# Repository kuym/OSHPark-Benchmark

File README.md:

# Interesting PCB designs

## L4

Device with Nordic nRF51822, muRata Type-1BD SiP (containing Broadcom BCM43362 WiFi silicon and STM32F405 microcontroller) plus ultra-low-power STM32L052.  BLE and WiFi RF paths are shared with an RF switch (Skyworks SKY13370.)

## BGA64-500um

Breakout for STM32 microcontroller in 64BGA (8x8 balls at 0.5mm pitch) to breadboard-friendly packaging.

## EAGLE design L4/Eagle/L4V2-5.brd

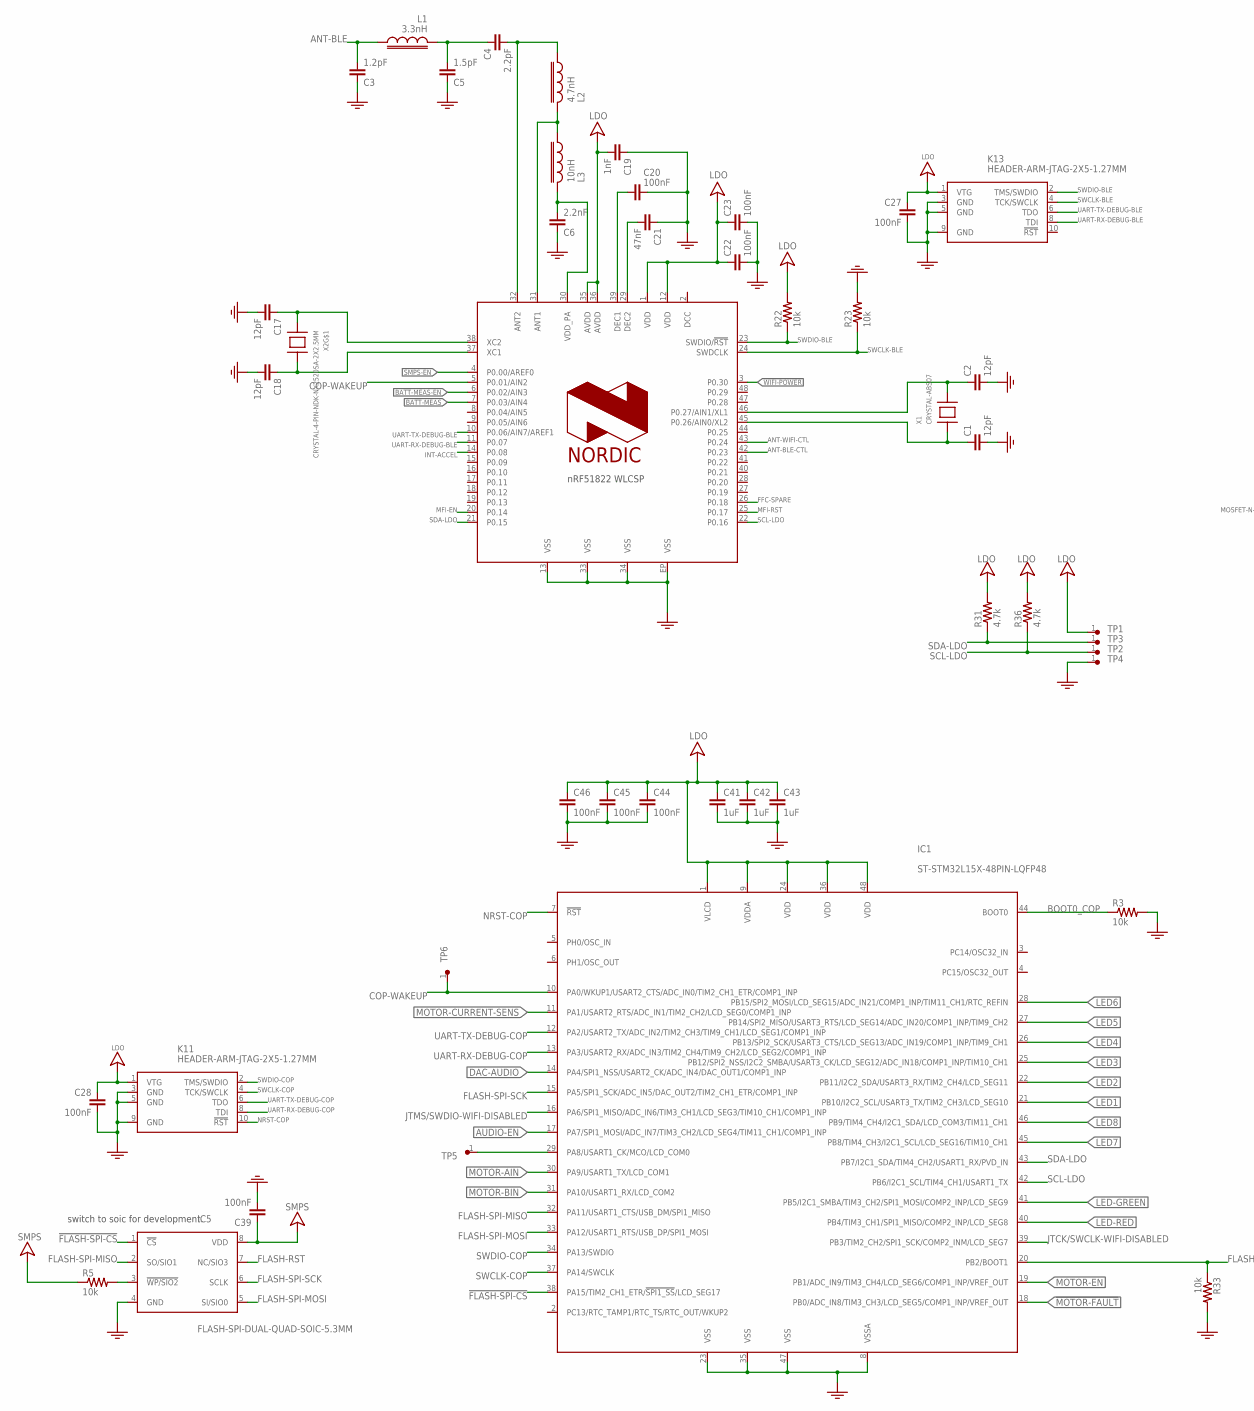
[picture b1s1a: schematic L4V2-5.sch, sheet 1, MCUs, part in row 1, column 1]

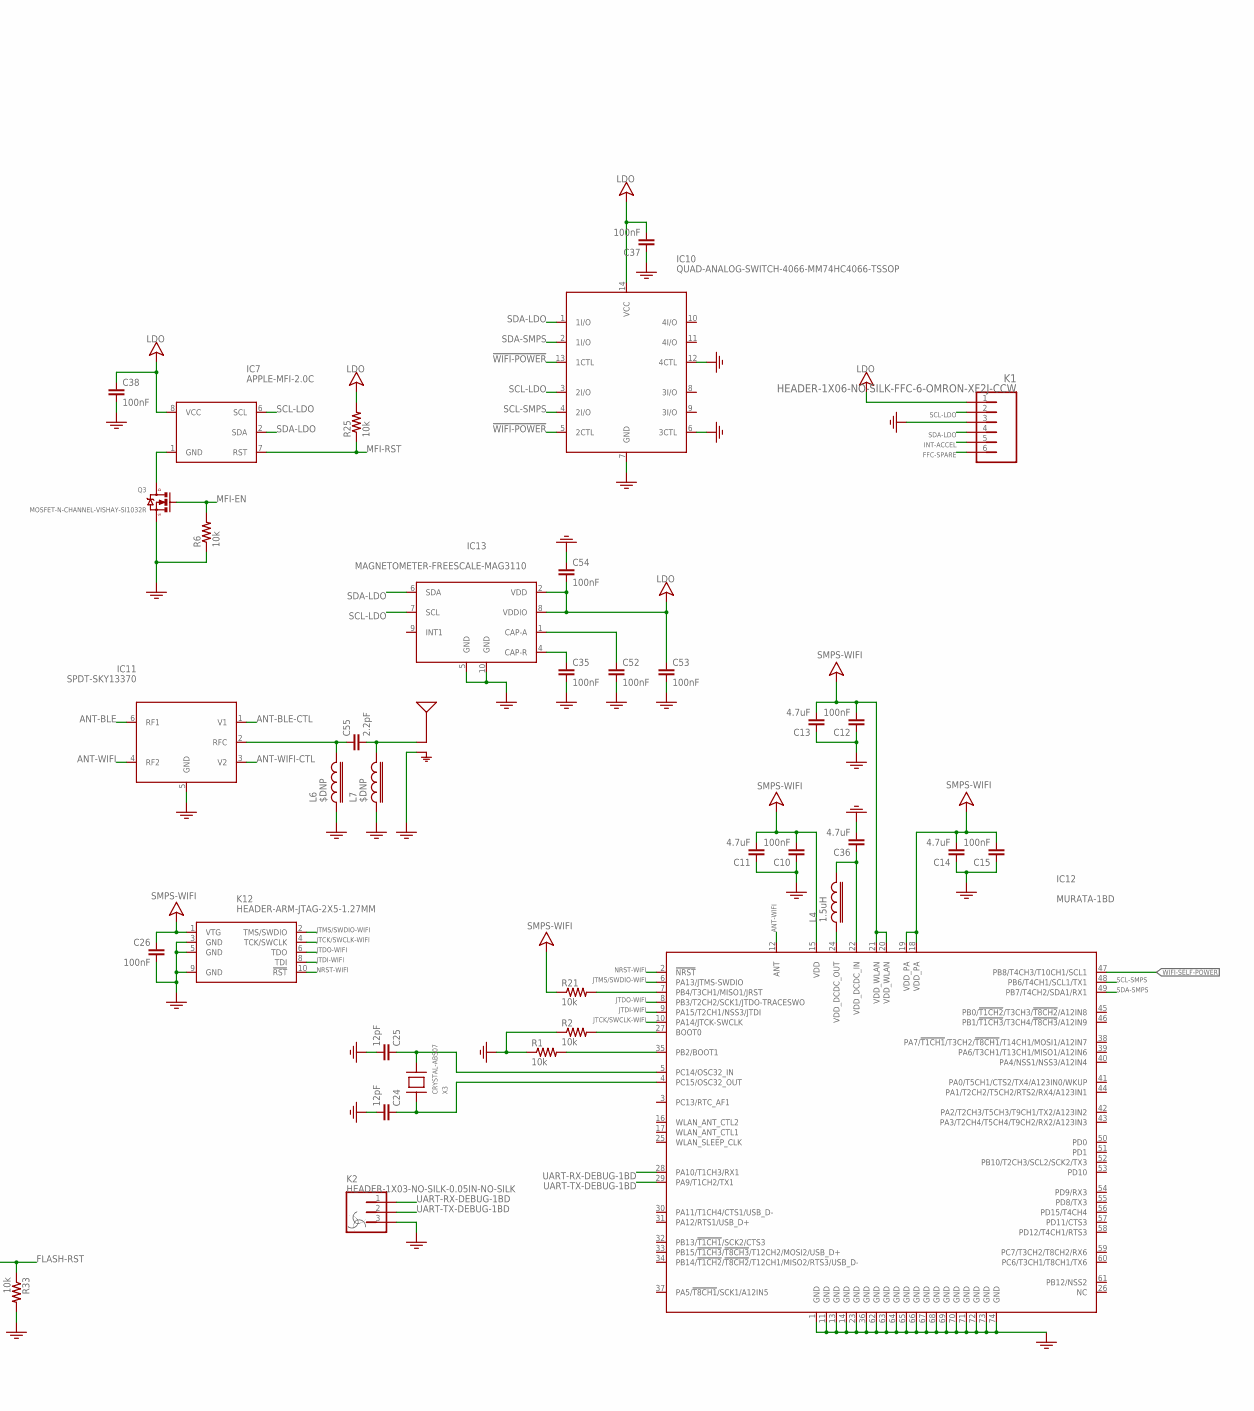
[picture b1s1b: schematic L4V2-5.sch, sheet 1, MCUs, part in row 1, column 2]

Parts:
ANT1: ANTENNA-WITH-GND-2.450GHZ-TI-AN043; ANTENNA-2.450GHZ-TI-AN043
C1, C2, C17, C18, C24, C25: 12pF; 0402
C3: 1.2pF; 0402
C4: 2.2pF; 0402
C5: 1.5pF; 0402
C6: 2.2nF; 0402
C10, C12, C15, C20, C22, C23, C26, C27, C28, C35, C37, C38, C39, C44, C45, C46, C52, C53, C54: 100nF; 0402
C11, C13, C14, C36: 4.7uF; 0402
C19: 1nF; 0402
C21: 47nF; 0402
C41, C42, C43: 1uF; 0402
C55: 2.2pF; 0402-MIN
IC1: ST-STM32L15X-48PIN-LQFP48; LQFP48-0.5MM
IC3: BLUETOOTH-4.0-SOC-NORDIC-NRF51822-QFN48; QFN48-5X5MM-0.4MM
IC5: FLASH-SPI-DUAL-QUAD-SOIC-5.3MM; SOIC8-5.3MM-MINIMAL
IC7: APPLE-MFI-2.0C; DFN8-2.5MMX2.5MM
IC10: QUAD-ANALOG-SWITCH-4066-MM74HC4066-TSSOP; TSSOP14
IC11: SPDT-SKY13370; DFN6-1.5MMX1.5MM
IC12: MURATA-1BD
IC13: MAGNETOMETER-FREESCALE-MAG3110; QFN10-2X2MM-FREESCALE-MAG3110
K1: HEADER-1X06-NO-SILK-FFC-6-OMRON-XF2J-CCW; HEADER-FFC-6-OMRON-XF2J-CCW
K2: HEADER-1X03-NO-SILK-0.05IN-NO-SILK; HEADER-1X03-0.05IN-NO-SILK
K11, K12, K13: HEADER-ARM-JTAG-2X5-1.27MM; HEADER-SMT-1.27MM-5X2-JTAG
L1: 3.3nH; 0402
L2: 4.7nH; 0402
L3: 10nH; 0402
L4: 1.5uH; 0805-WIDE
L6, L7: $DNP; 0402-MIN
Q3: MOSFET-N-CHANNEL-VISHAY-SI1032R; SC-75A
R1, R2, R3, R5, R6, R21, R22, R23, R25, R33: 10k; 0402
R31, R36: 4.7k; 0402
TP1, TP2, TP3, TP4, TP5, TP6: $DNP; TEST-POINT-0.75MM
X1, X3: CRYSTAL-ABS07; 1206-MIN
X2: CRYSTAL-4-PIN-NDK-NX2520SA-2X2.5MM; CRYSTAL-NDK-NX2025SA-2X2.5MM

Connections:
16MHZ-XTAL-IN: C18.2, IC3.37 (XC1), X2.1
16MHZ-XTAL-OUT: C17.2, IC3.38 (XC2), X2.3
32KHZ-XTAL-IN-BLE: C2.2, IC3.46 (P0.27/AIN1/XL1), X1.2
32KHZ-XTAL-IN-WIFI: C25.2, IC12.5 (PC14/OSC32_IN), X3.2
32KHZ-XTAL-OUT-BLE: C1.2, IC3.45 (P0.26/AIN0/XL2), X1.1
32KHZ-XTAL-OUT-WIFI: C24.2, IC12.4 (PC15/OSC32_OUT), X3.1
!FLASH-SPI-CS: IC1.38 (PA15/TIM2_CH1_ETR/!SPI1_SS!/LCD_SEG17), IC5.1 (!CS)
!MOTOR-FAULT: IC1.18 (PB0/ADC_IN8/TIM3_CH3/LCD_SEG5/COMP1_INP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); also elsewhere on the board
!WIFI-POWER: IC3.3 (P0.30), IC10.5 (2CTL), IC10.13 (1CTL); also elsewhere on the board
ANT-BLE: C3.1, IC11.6 (RF1), L1.2
ANT-BLE-CTL: IC3.42 (P0.23), IC11.1 (V1)
ANT-WIFI: IC11.4 (RF2), IC12.12 (ANT)
ANT-WIFI-CTL: IC3.43 (P0.24), IC11.3 (V2)
AUDIO-EN: IC1.17 (PA7/SPI1_MOSI/ADC_IN7/TIM3_CH2/LCD_SEG4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); also elsewhere on the board
BATT-MEAS: IC3.7 (P0.03/AIN4); also elsewhere on the board
BATT-MEAS-EN: IC3.6 (P0.02/AIN3); also elsewhere on the board
BOOT0_COP: IC1.44 (BOOT0), R3.1
COP-WAKEUP: IC1.10 (PA0/WKUP1/USART2_CTS/ADC_IN0/TIM2_CH1_E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), IC3.5 (P0.01/AIN2), TP6.1
DAC-AUDIO: IC1.14 (PA4/SPI1_NSS/USART2_CK/ADC_IN4/DAC_OUT1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); also elsewhere on the board
FFC-SPARE: IC3.26 (P0.18), K1.6
FLASH-RST: IC1.20 (PB2/BOOT1), IC5.7 (NC/SIO3), R33.1
FLASH-SPI-MISO: IC1.32 (PA11/USART1_CTS/USB_DM/SPI1_MISO), IC5.2 (SO/SIO1)
FLASH-SPI-MOSI: IC1.33 (PA12/USART1_RTS/USB_DP/SPI1_MOSI), IC5.5 (SI/SIO0)
FLASH-SPI-SCK: IC1.15 (PA5/SPI1_SCK/ADC_IN5/DAC_OUT2/TIM2_CH1_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), IC5.6 (SCLK)
GND: ANT1.RFGND (GND), C1.1, C2.1, C3.2, C5.2, C6.2, C10.2, C11.2, C12.2, C13.2, C14.2, C15.2, C17.1, C18.1, C19.2, C20.2, C21.2, C22.1, C23.1, C24.1, C25.1, C26.1, C27.1, C28.1, C35.1, C36.1, C37.2, C38.1, C39.1, C41.1, C42.1, C43.1, C44.1, C45.1, C46.1, C52.1, C53.1, C54.2, IC1.8 (VSSA), IC1.23 (VSS), IC1.35 (VSS), IC1.47 (VSS), IC3.13 (VSS), IC3.33 (VSS), IC3.34 (VSS), IC3.EP (VSS), IC5.4 (GND), IC10.6 (3CTL), IC10.7 (GND), IC10.12 (4CTL), IC11.5 (GND), IC12.1 (GND), IC12.11 (GND), IC12.13 (GND), IC12.14 (GND), IC12.23 (GND), IC12.36 (GND), IC12.62 (GND), IC12.63 (GND), IC12.64 (GND), IC12.65 (GND), IC12.66 (GND), IC12.67 (GND), IC12.68 (GND), IC12.69 (GND), IC12.70 (GND), IC12.71 (GND), IC12.72 (GND), IC12.73 (GND), IC12.74 (GND), IC13.5 (GND), IC13.10 (GND), K1.3, K2.3, K11.3 (GND), K11.5 (GND), K11.9 (GND), K12.3 (GND), K12.5 (GND), K12.9 (GND), K13.3 (GND), K13.5 (GND), K13.9 (GND), L6.1, L7.1, Q3.2 (SOURCE), R1.1, R2.1, R3.2, R6.1, R23.2, R33.2, TP4.1; also elsewhere on the board
INT-ACCEL: IC3.14 (P0.08), K1.5
JRST-WIFI: IC12.7 (PB4/T3CH1/MISO1/JRST), R21.2
JTCK/SWCLK-WIFI: IC12.10 (PA14/JTCK-SWCLK), K12.4 (TCK/SWCLK)
JTCK/SWCLK-WIFI-DISABLED: IC1.39 (PB3/TIM2_CH2/SPI1_SCK/COMP2_INM/LCD_SEG7)
JTDI-WIFI: IC12.9 (PA15/T2CH1/NSS3/JTDI), K12.8 (TDI)
JTDO-WIFI: IC12.8 (PB3/T2CH2/SCK1/JTDO-TRACESWO), K12.6 (TDO)
JTMS/SWDIO-WIFI: IC12.6 (PA13/JTMS-SWDIO), K12.2 (TMS/SWDIO)
JTMS/SWDIO-WIFI-DISABLED: IC1.16 (PA6/SPI1_MISO/ADC_IN6/TIM3_CH1/LCD_SEG3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)
LDO: C19.1, C22.2, C23.2, C27.2, C28.2, C37.1, C38.2, C41.2, C42.2, C43.2, C44.2, C45.2, C46.2, C53.2, C54.1, IC1.1 (VLCD), IC1.9 (VDDA), IC1.24 (VDD), IC1.36 (VDD), IC1.48 (VDD), IC3.1 (VDD), IC3.12 (VDD), IC3.35 (AVDD), IC3.36 (AVDD), IC7.8 (VCC), IC10.14 (VCC), IC13.2 (VDD), IC13.8 (VDDIO), K1.1, K11.1 (VTG), K13.1 (VTG), R22.2, R25.2, R31.2, R36.2, TP1.1; also elsewhere on the board
LED1: IC1.21 (PB10/I2C2_SCL/USART3_TX/TIM2_CH3/LCD_SE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); also elsewhere on the board
LED2: IC1.22 (PB11/I2C2_SDA/USART3_RX/TIM2_CH4/LCD_SE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); also elsewhere on the board
LED3: IC1.25 (PB12/SPI2_NSS/I2C2_SMBA/USART3_CK/LCD_S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); also elsewhere on the board
LED4: IC1.26 (PB13/SPI2_SCK/USART3_CTS/LCD_SEG13/ADC_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); also elsewhere on the board
LED5: IC1.27 (PB14/SPI2_MISO/USART3_RTS/LCD_SEG14/ADC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); also elsewhere on the board
LED6: IC1.28 (PB15/SPI2_MOSI/LCD_SEG15/ADC_IN21/COMP1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); also elsewhere on the board
LED7: IC1.45 (PB8/TIM4_CH3/I2C1_SCL/LCD_SEG16/TIM10_C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); also elsewhere on the board
LED8: IC1.46 (PB9/TIM4_CH4/I2C1_SDA/LCD_COM3/TIM11_CH1); also elsewhere on the board
LED-GREEN: IC1.41 (PB5/I2C1_SMBA/TIM3_CH2/SPI1_MOSI/COMP2_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); also elsewhere on the board
LED-RED: IC1.40 (PB4/TIM3_CH1/SPI1_MISO/COMP2_INP/LCD_SE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); also elsewhere on the board
MFI-EN: IC3.20 (P0.14), Q3.1 (GATE), R6.2
MFI-RST: IC3.25 (P0.17), IC7.7 (RST), R25.1
MOTOR-AIN: IC1.30 (PA9/USART1_TX/LCD_COM1); also elsewhere on the board
MOTOR-BIN: IC1.31 (PA10/USART1_RX/LCD_COM2); also elsewhere on the board
MOTOR-CURRENT-SENS: IC1.11 (PA1/USART2_RTS/ADC_IN1/TIM2_CH2/LCD_SEG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); also elsewhere on the board
MOTOR-EN: IC1.19 (PB1/ADC_IN9/TIM3_CH4/LCD_SEG6/COMP1_INP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); also elsewhere on the board
unnamed: C20.1, IC3.39 (DEC1)
unnamed: IC3.31 (ANT1), L2.1, L3.2
unnamed: C55.2, IC11.2 (RFC), L6.2
unnamed: C4.1, IC3.32 (ANT2), L2.2
unnamed: C4.2, C5.1, L1.1
unnamed: IC12.27 (BOOT0), R2.2
unnamed: IC12.24 (VDD_DCDC_OUT), L4.1
unnamed: C21.1, IC3.29 (DEC2)
unnamed: IC12.35 (PB2/BOOT1), R1.2
unnamed: IC5.3 (!WP/SIO2), R5.2
unnamed: ANT1.ANT (RF), C55.1, L7.2
unnamed: IC7.1 (GND), Q3.3 (DRAIN)
unnamed: IC1.29 (PA8/USART1_CK/MCO/LCD_COM0), TP5.1
unnamed: C6.1, IC3.30 (VDD_PA), L3.1
unnamed: C36.2, IC12.22 (VDD_DCDC_IN), L4.2
unnamed: C35.2, IC13.4 (CAP-R)
unnamed: C52.2, IC13.1 (CAP-A)
NRST-COP: IC1.7 (!RST), K11.10 (!RST)
NRST-WIFI: IC12.2 (!NRST), K12.10 (!RST)
SCL-LDO: IC1.42 (PB6/I2C1_SCL/TIM4_CH1/USART1_TX), IC3.22 (P0.16), IC7.6 (SCL), IC10.3 (2I/O), IC13.7 (SCL), K1.2, R36.1, TP2.1
SCL-SMPS: IC10.4 (2I/O), IC12.48 (PB6/T4CH1/SCL1/TX1)
SDA-LDO: IC1.43 (PB7/I2C1_SDA/TIM4_CH2/USART1_RX/PVD_IN), IC3.21 (P0.15), IC7.2 (SDA), IC10.1 (1I/O), IC13.6 (SDA), K1.4, R31.1, TP3.1
SDA-SMPS: IC10.2 (1I/O), IC12.49 (PB7/T4CH2/SDA1/RX1)
SMPS: C39.2, IC5.8 (VDD), R5.1; also elsewhere on the board
SMPS-EN: IC3.4 (P0.00/AREF0); also elsewhere on the board
SMPS-WIFI: C10.1, C11.1, C12.1, C13.1, C14.1, C15.1, C26.2, IC12.15 (VDD), IC12.18 (VDD_PA), IC12.19 (VDD_PA), IC12.20 (VDD_WLAN), IC12.21 (VDD_WLAN), K12.1 (VTG), R21.1; also elsewhere on the board
SWCLK-BLE: IC3.24 (SWDCLK), K13.4 (TCK/SWCLK), R23.1
SWCLK-COP: IC1.37 (PA14/SWCLK), K11.4 (TCK/SWCLK)
SWDIO-BLE: IC3.23 (SWDIO/!RST), K13.2 (TMS/SWDIO), R22.1
SWDIO-COP: IC1.34 (PA13/SWDIO), K11.2 (TMS/SWDIO)
UART-RX-DEBUG-1BD: IC12.28 (PA10/T1CH3/RX1), K2.1
UART-RX-DEBUG-BLE: IC3.11 (P0.07), K13.8 (TDI)
UART-RX-DEBUG-COP: IC1.13 (PA3/USART2_RX/ADC_IN3/TIM2_CH4/TIM9_CH2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), K11.8 (TDI)
UART-TX-DEBUG-1BD: IC12.29 (PA9/T1CH2/TX1), K2.2
UART-TX-DEBUG-BLE: IC3.10 (P0.06/AIN7/AREF1), K13.6 (TDO)
UART-TX-DEBUG-COP: IC1.12 (PA2/USART2_TX/ADC_IN2/TIM2_CH3/TIM9_CH1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), K11.6 (TDO)
WIFI-SELF-POWER: IC12.47 (PB8/T4CH3/T10CH1/SCL1); also elsewhere on the board

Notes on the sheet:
switch to soic for development.

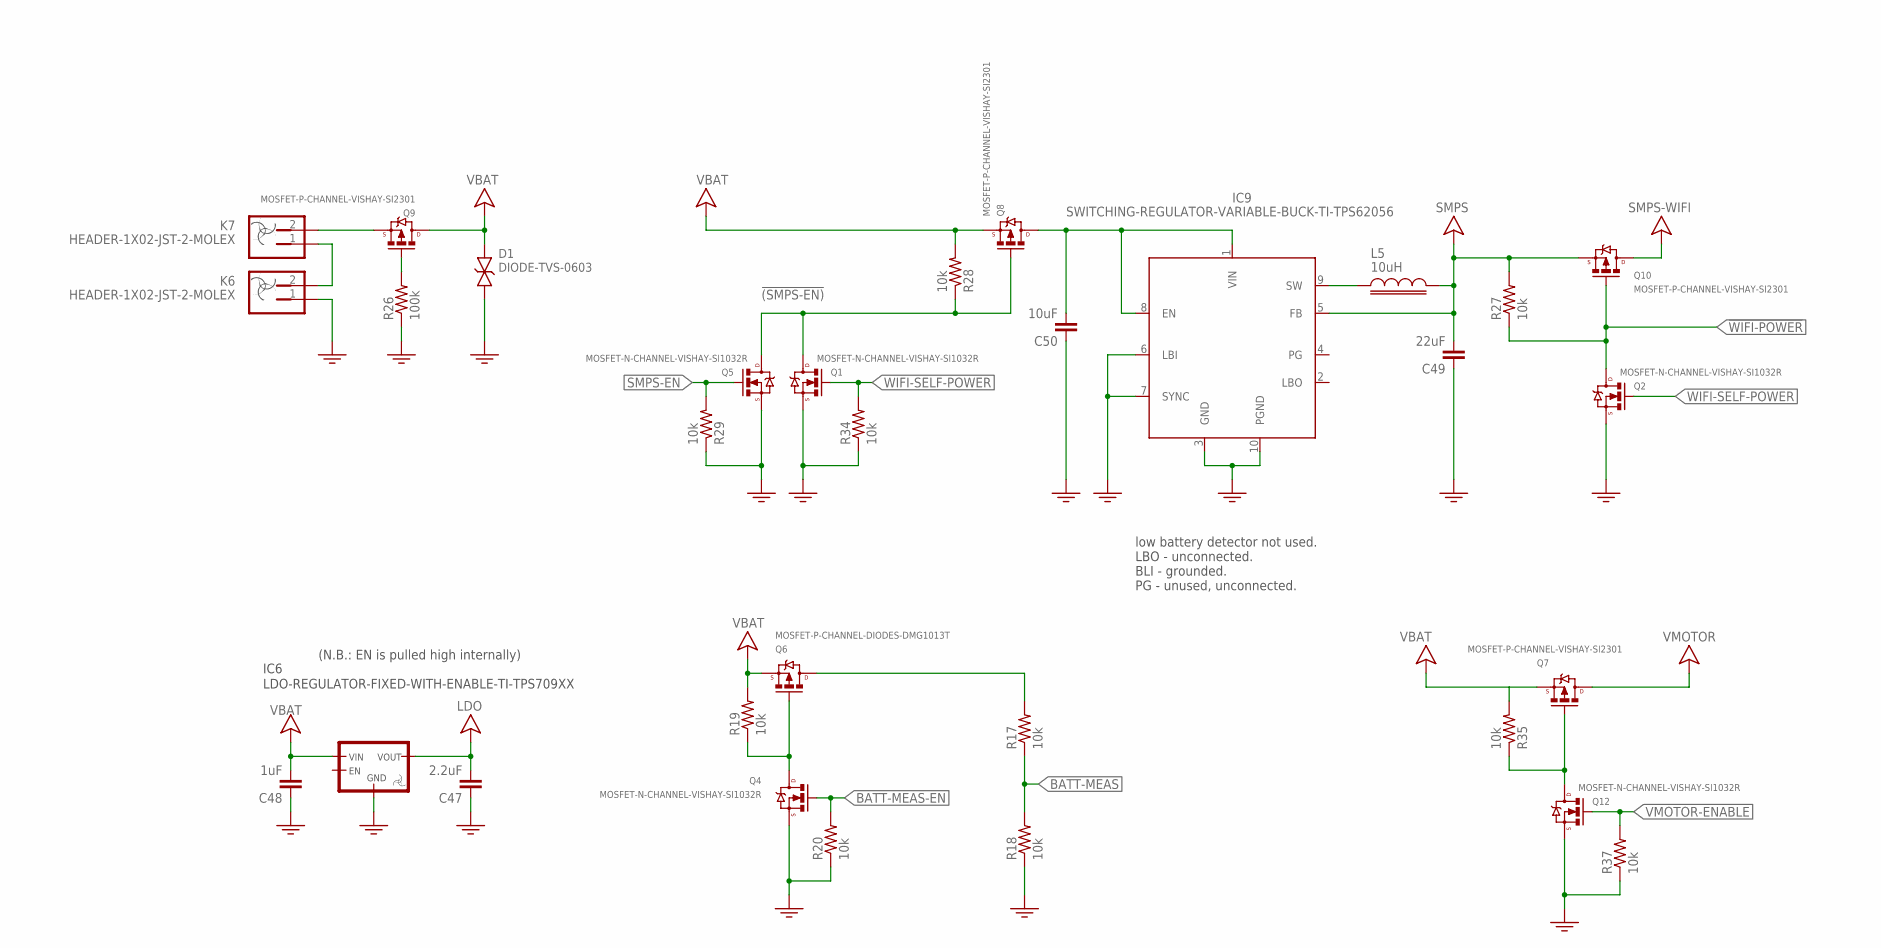
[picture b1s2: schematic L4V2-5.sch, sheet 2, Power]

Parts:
C47: 2.2uF; 0402
C48: 1uF; 0402
C49: 22uF; 0805-MIN
C50: 10uF; 0805-MIN
D1: DIODE-TVS-0603; 0603
IC6: LDO-REGULATOR-FIXED-WITH-ENABLE-TI-TPS709XX; SOT23-5
IC9: SWITCHING-REGULATOR-VARIABLE-BUCK-TI-TPS62056; VSSOP10
K6, K7: HEADER-1X02-JST-2-MOLEX; HEADER-JST-2-MOLEX-53261-0271
L5: 10uH; 1210-INDUCTOR-MIN
Q1, Q2, Q4, Q5, Q12: MOSFET-N-CHANNEL-VISHAY-SI1032R; SC-75A
Q6: MOSFET-P-CHANNEL-DIODES-DMG1013T; SC-75A
Q7, Q8, Q9, Q10: MOSFET-P-CHANNEL-VISHAY-SI2301; SOT23-3
R17, R18, R19, R20, R27, R28, R29, R34, R35, R37: 10k; 0402
R26: 100k; 0402

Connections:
!(SMPS-EN): Q1.3 (DRAIN), Q5.3 (DRAIN), Q8.1 (GATE), R28.1
!(VMOTOR-EN): Q7.1 (GATE), Q12.3 (DRAIN), R35.1
!WIFI-POWER: Q2.3 (DRAIN), Q10.1 (GATE), R27.1; also elsewhere on the board
BATT-MEAS: R17.1, R18.2; also elsewhere on the board
BATT-MEAS-EN: Q4.1 (GATE), R20.2; also elsewhere on the board
GND: C47.2, C48.2, C49.2, C50.2, D1.1, IC6.2 (GND), IC9.3 (GND), IC9.6 (LBI), IC9.7 (SYNC), IC9.10 (PGND), K6.1, Q1.2 (SOURCE), Q2.2 (SOURCE), Q4.2 (SOURCE), Q5.2 (SOURCE), Q12.2 (SOURCE), R18.1, R20.1, R26.1, R29.1, R34.1, R37.1; also elsewhere on the board
LDO: C47.1, IC6.5 (VOUT); also elsewhere on the board
unnamed: Q4.3 (DRAIN), Q6.1 (GATE), R19.1
unnamed: Q6.3 (DRAIN), R17.2
unnamed: K6.2, K7.1
unnamed: Q9.1 (GATE), R26.2
unnamed: IC9.9 (SW), L5.1
SMPS: C49.1, IC9.5 (FB), L5.2, Q10.2 (SOURCE), R27.2; also elsewhere on the board
SMPS-EN: Q5.1 (GATE), R29.2; also elsewhere on the board
SMPS-IN: C50.1, IC9.1 (VIN), IC9.8 (EN), Q8.3 (DRAIN)
SMPS-WIFI: Q10.3 (DRAIN); also elsewhere on the board
VBAT: C48.1, D1.2, IC6.1 (VIN), Q6.2 (SOURCE), Q7.2 (SOURCE), Q8.2 (SOURCE), Q9.3 (DRAIN), R19.2, R28.2, R35.2
VBAT-RAW: K7.2, Q9.2 (SOURCE)
VMOTOR: Q7.3 (DRAIN); also elsewhere on the board
VMOTOR-ENABLE: Q12.1 (GATE), R37.2
WIFI-SELF-POWER: Q1.1 (GATE), Q2.1 (GATE), R34.2; also elsewhere on the board

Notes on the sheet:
low battery detector not used. LBO - unconnected. BLI - grounded. PG - unused, unconnected.
(N.B.: EN is pulled high internally)

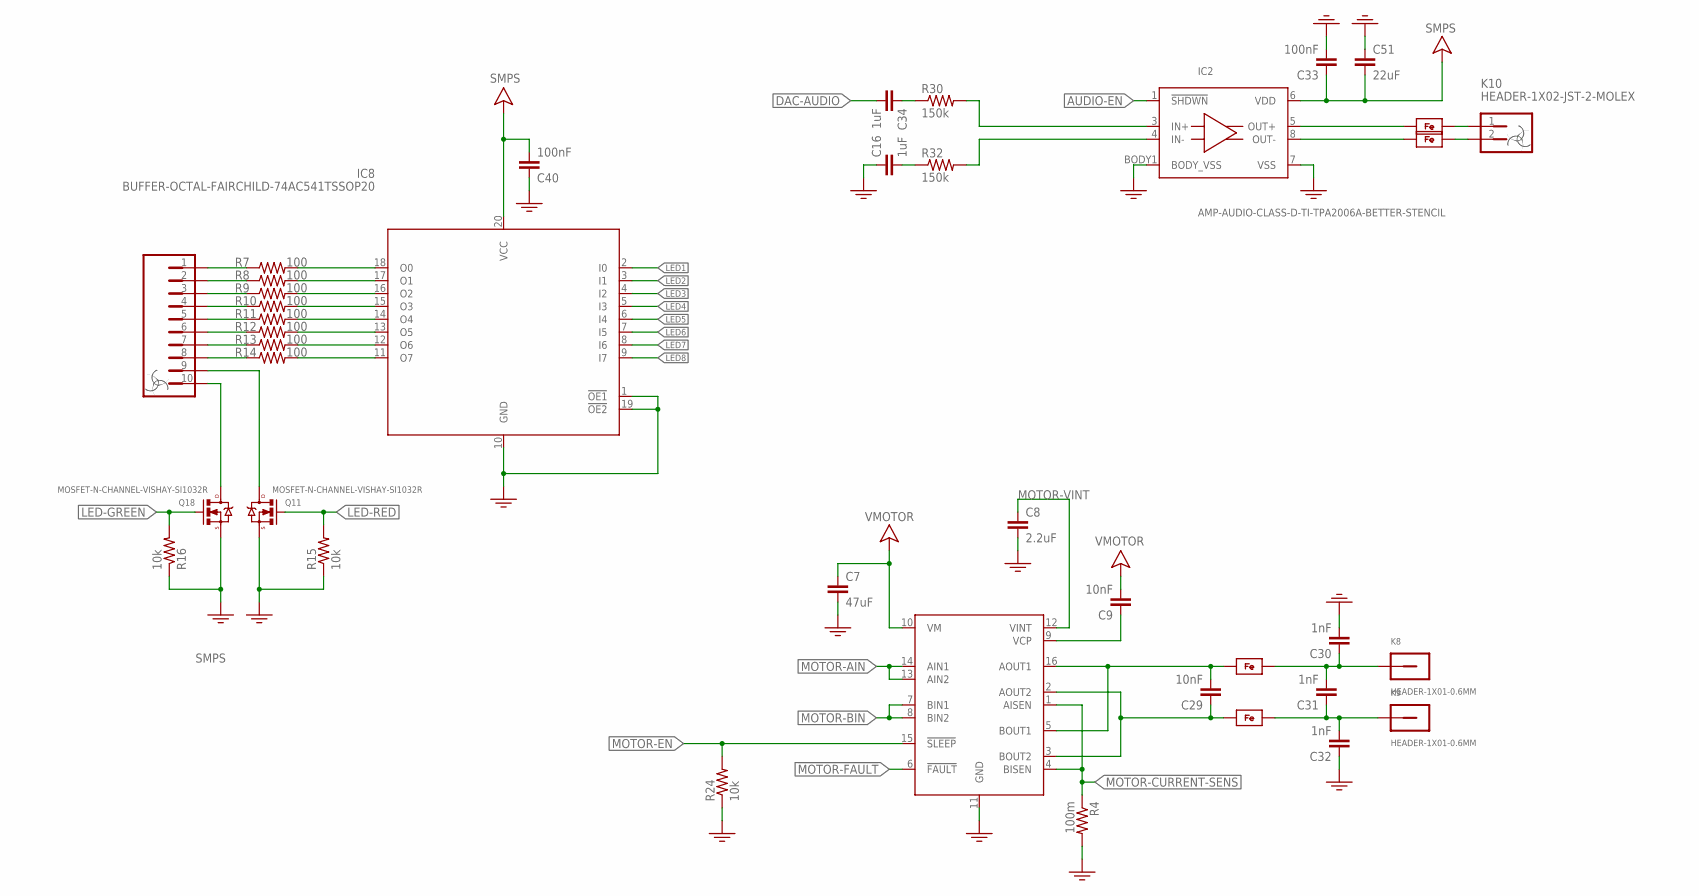
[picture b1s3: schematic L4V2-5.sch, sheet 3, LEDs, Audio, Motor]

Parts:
C7: 47uF; 1206-MIN
C8: 2.2uF; 0603-MIN
C9, C29: 10nF; 0402
C16, C34: 1uF; 0402
C30, C31, C32: 1nF; 0402
C33, C40: 100nF; 0402
C51: 22uF; 0805-MIN
FB1, FB2: FERRITE-0805; 0805-MIN
FB3, FB4: FERRITE-0603; 0603-MIN
IC2: AMP-AUDIO-CLASS-D-TI-TPA2006A-BETTER-STENCIL; QFN8-3X3MM-TI-TPA200X-BETTER-STENCIL
IC4: MOTOR-DRIVER-TI-DRV8833; QFN16-4X4MM-0.65MM
IC8: BUFFER-OCTAL-FAIRCHILD-74AC541TSSOP20; TSSOP20
K3: HEADER-1X10-NO-SILK-1.27MM; HEADER-1X10-1.27MM
K8, K9: HEADER-1X01-0.6MM; HEADER-1X01-0.6MM-DIAM
K10: HEADER-1X02-JST-2-MOLEX; HEADER-JST-2-MOLEX-53261-0271
Q11, Q18: MOSFET-N-CHANNEL-VISHAY-SI1032R; SC-75A
R4: 100m; 0603
R7, R8, R9, R10, R11, R12, R13, R14: 100; 0402-MIN
R15, R16: 10k; 0402-MIN
R24: 10k; 0402
R30, R32: 150k; 0402

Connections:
!MOTOR-FAULT: IC4.6 (!FAULT); also elsewhere on the board
AUDIO-EN: IC2.1 (!SHDWN); also elsewhere on the board
DAC-AUDIO: C34.1; also elsewhere on the board
GND: C7.1, C8.1, C16.2, C30.1, C32.2, C33.1, C40.2, C51.2, IC2.7 (VSS), IC2.BODY1 (BODY_VSS), IC4.11 (GND), IC8.1 (!OE1), IC8.10 (GND), IC8.19 (!OE2), Q11.2 (SOURCE), Q18.2 (SOURCE), R4.2, R15.1, R16.1, R24.1; also elsewhere on the board
LED1: IC8.2 (I0); also elsewhere on the board
LED2: IC8.3 (I1); also elsewhere on the board
LED3: IC8.4 (I2); also elsewhere on the board
LED4: IC8.5 (I3); also elsewhere on the board
LED5: IC8.6 (I4); also elsewhere on the board
LED6: IC8.7 (I5); also elsewhere on the board
LED7: IC8.8 (I6); also elsewhere on the board
LED8: IC8.9 (I7); also elsewhere on the board
LED-GREEN: Q18.1 (GATE), R16.2; also elsewhere on the board
LED-RED: Q11.1 (GATE), R15.2; also elsewhere on the board
MOTOR-AIN: IC4.13 (AIN2), IC4.14 (AIN1); also elsewhere on the board
MOTOR-BIN: IC4.7 (BIN1), IC4.8 (BIN2); also elsewhere on the board
MOTOR-CURRENT-SENS: IC4.1 (AISEN), IC4.4 (BISEN), R4.1; also elsewhere on the board
MOTOR-EN: IC4.15 (!SLEEP), R24.2; also elsewhere on the board
MOTOR-OUT1: C29.1, FB1.1, IC4.5 (BOUT1), IC4.16 (AOUT1)
MOTOR-OUT2: C29.2, FB2.1, IC4.2 (AOUT2), IC4.3 (BOUT2)
MOTOR-VCP: C9.2, IC4.9 (VCP)
MOTOR-VINT: C8.2, IC4.12 (VINT)
unnamed: FB4.2, K10.2
unnamed: C30.2, C31.1, FB1.2, K8.P$1
unnamed: IC8.18 (O0), R7.2
unnamed: C31.2, C32.1, FB2.2, K9.P$1
unnamed: IC8.15 (O3), R10.2
unnamed: FB3.2, K10.1
unnamed: IC8.17 (O1), R8.2
unnamed: FB3.1, IC2.5 (OUT+)
unnamed: FB4.1, IC2.8 (OUT-)
unnamed: IC2.3 (IN+), R30.2
unnamed: IC2.4 (IN-), R32.2
unnamed: IC8.13 (O5), R12.2
unnamed: K3.10, Q18.3 (DRAIN)
unnamed: C34.2, R30.1
unnamed: C16.1, R32.1
unnamed: K3.9, Q11.3 (DRAIN)
unnamed: K3.1, R7.1
unnamed: K3.2, R8.1
unnamed: K3.3, R9.1
unnamed: K3.4, R10.1
unnamed: K3.5, R11.1
unnamed: K3.6, R12.1
unnamed: K3.7, R13.1
unnamed: K3.8, R14.1
unnamed: IC8.16 (O2), R9.2
unnamed: IC8.14 (O4), R11.2
unnamed: IC8.12 (O6), R13.2
unnamed: IC8.11 (O7), R14.2
SMPS: C33.2, C40.1, C51.1, IC2.6 (VDD), IC8.20 (VCC); also elsewhere on the board
VMOTOR: C7.2, C9.1, IC4.10 (VM); also elsewhere on the board

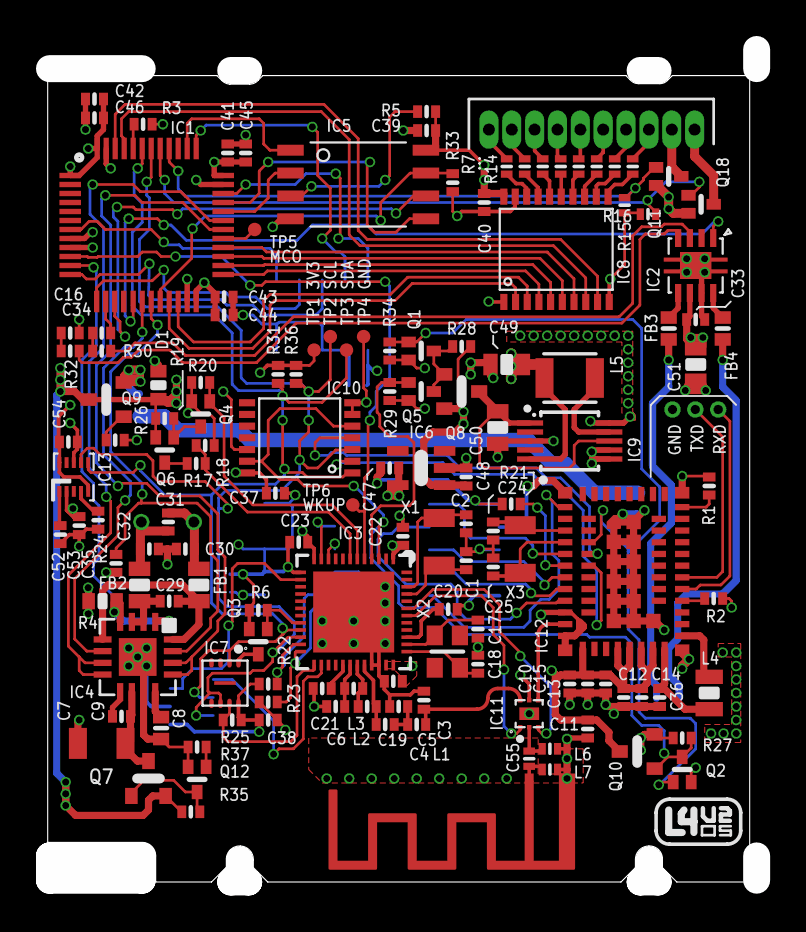
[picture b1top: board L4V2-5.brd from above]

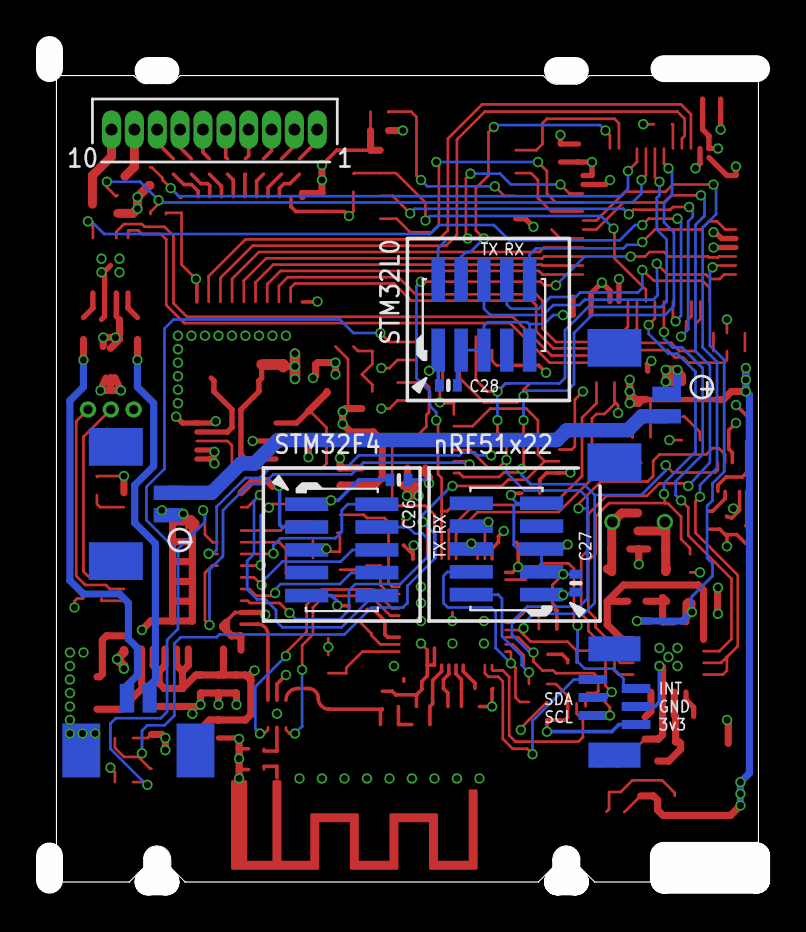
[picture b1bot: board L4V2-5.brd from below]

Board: 4 copper layers, 39.4 x 46.2 mm, 152 parts (10 on the bottom side), 129 nets.

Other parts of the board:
U$34: MECH-OUTLINE

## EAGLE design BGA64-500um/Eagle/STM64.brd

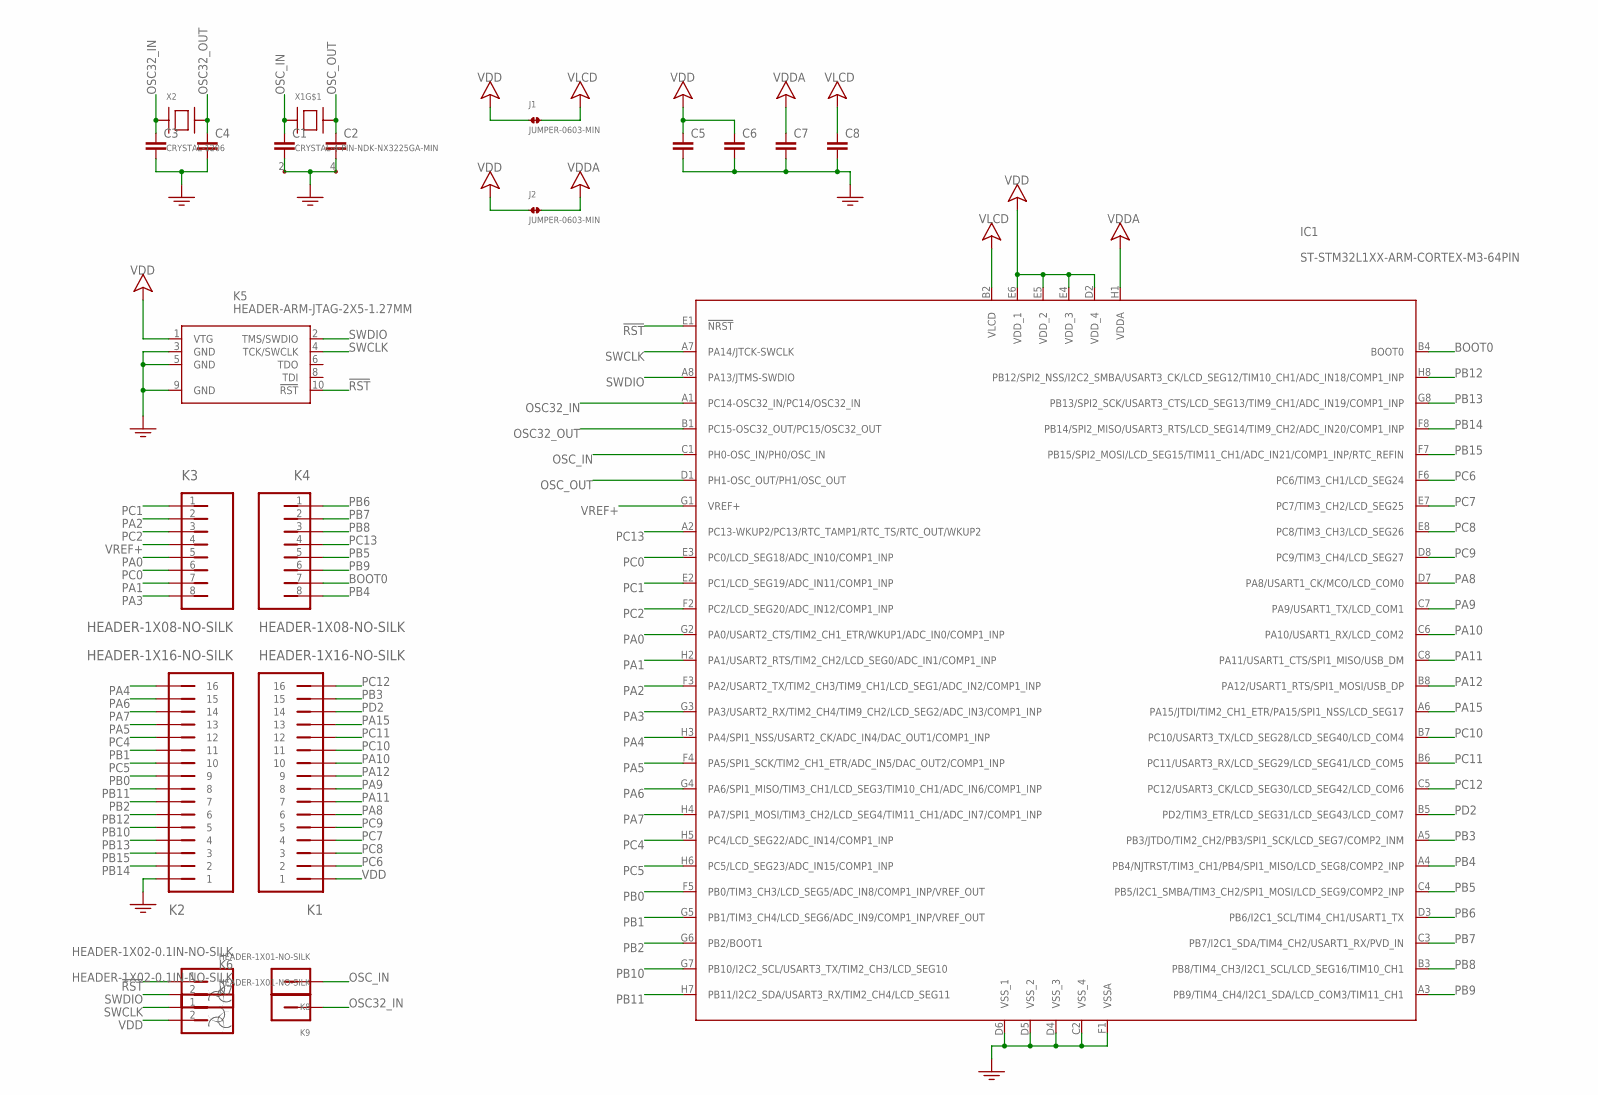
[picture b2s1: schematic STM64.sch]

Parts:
C1, C2, C3, C4, C5, C6, C7, C8: CAP-0402-MIN; 0402-MIN
IC1: ST-STM32L1XX-ARM-CORTEX-M3-64PIN; BGA64-5X5MM-0.5MM
J1, J2: JUMPER-0603-MIN; 0603-MIN-JUMPER
K1, K2: HEADER-1X16-NO-SILK
K3, K4: HEADER-1X08-NO-SILK
K5: HEADER-ARM-JTAG-2X5-1.27MM; HEADER-SMT-1.27MM-5X2-JTAG
K6, K7: HEADER-1X02-0.1IN-NO-SILK; HEADER-1X02-NO-SILK
K8, K9: HEADER-1X01-NO-SILK
X1: CRYSTAL-4-PIN-NDK-NX3225GA-MIN; CRYSTAL-NDK-NX3225GA-3X2.5MM-MIN
X2: CRYSTAL-1206; 1206-MIN

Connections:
!RST: IC1.E1 (!NRST), K5.10 (!RST), K6.1
BOOT0: IC1.B4 (BOOT0), K4.7
GND: C1.1, C2.1, C3.1, C4.1, C5.1, C6.1, C7.1, C8.1, IC1.C2 (VSS_4), IC1.D4 (VSS_3), IC1.D5 (VSS_2), IC1.D6 (VSS_1), IC1.F1 (VSSA), K2.1, K5.3 (GND), K5.5 (GND), K5.9 (GND), X1.2 (1), X1.4 (1)
OSC32_IN: C3.2, IC1.A1 (PC14-OSC32_IN/PC14/OSC32_IN), K9.1, X2.1
OSC32_OUT: C4.2, IC1.B1 (PC15-OSC32_OUT/PC15/OSC32_OUT), X2.2
OSC_IN: C1.2, IC1.C1 (PH0-OSC_IN/PH0/OSC_IN), K8.1, X1.1
OSC_OUT: C2.2, IC1.D1 (PH1-OSC_OUT/PH1/OSC_OUT), X1.3
PA0: IC1.G2 (PA0/USART2_CTS/TIM2_CH1_ETR/WKUP1/ADC_I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), K3.5
PA1: IC1.H2 (PA1/USART2_RTS/TIM2_CH2/LCD_SEG0/ADC_IN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), K3.7
PA2: IC1.F3 (PA2/USART2_TX/TIM2_CH3/TIM9_CH1/LCD_SEG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), K3.2
PA3: IC1.G3 (PA3/USART2_RX/TIM2_CH4/TIM9_CH2/LCD_SEG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), K3.8
PA4: IC1.H3 (PA4/SPI1_NSS/USART2_CK/ADC_IN4/DAC_OUT1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), K2.16
PA5: IC1.F4 (PA5/SPI1_SCK/TIM2_CH1_ETR/ADC_IN5/DAC_O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), K2.13
PA6: IC1.G4 (PA6/SPI1_MISO/TIM3_CH1/LCD_SEG3/TIM10_C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), K2.15
PA7: IC1.H4 (PA7/SPI1_MOSI/TIM3_CH2/LCD_SEG4/TIM11_C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), K2.14
PA8: IC1.D7 (PA8/USART1_CK/MCO/LCD_COM0), K1.6
PA9: IC1.C7 (PA9/USART1_TX/LCD_COM1), K1.8
PA10: IC1.C6 (PA10/USART1_RX/LCD_COM2), K1.10
PA11: IC1.C8 (PA11/USART1_CTS/SPI1_MISO/USB_DM), K1.7
PA12: IC1.B8 (PA12/USART1_RTS/SPI1_MOSI/USB_DP), K1.9
PA15: IC1.A6 (PA15/JTDI/TIM2_CH1_ETR/PA15/SPI1_NSS/LC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), K1.13
PB0: IC1.F5 (PB0/TIM3_CH3/LCD_SEG5/ADC_IN8/COMP1_INP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), K2.9
PB1: IC1.G5 (PB1/TIM3_CH4/LCD_SEG6/ADC_IN9/COMP1_INP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), K2.11
PB2: IC1.G6 (PB2/BOOT1), K2.7
PB3: IC1.A5 (PB3/JTDO/TIM2_CH2/PB3/SPI1_SCK/LCD_SEG7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), K1.15
PB4: IC1.A4 (PB4/NJTRST/TIM3_CH1/PB4/SPI1_MISO/LCD_S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), K4.8
PB5: IC1.C4 (PB5/I2C1_SMBA/TIM3_CH2/SPI1_MOSI/LCD_SE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), K4.5
PB6: IC1.D3 (PB6/I2C1_SCL/TIM4_CH1/USART1_TX), K4.1
PB7: IC1.C3 (PB7/I2C1_SDA/TIM4_CH2/USART1_RX/PVD_IN), K4.2
PB8: IC1.B3 (PB8/TIM4_CH3/I2C1_SCL/LCD_SEG16/TIM10_C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), K4.3
PB9: IC1.A3 (PB9/TIM4_CH4/I2C1_SDA/LCD_COM3/TIM11_CH1), K4.6
PB10: IC1.G7 (PB10/I2C2_SCL/USART3_TX/TIM2_CH3/LCD_SE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), K2.5
PB11: IC1.H7 (PB11/I2C2_SDA/USART3_RX/TIM2_CH4/LCD_SE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), K2.8
PB12: IC1.H8 (PB12/SPI2_NSS/I2C2_SMBA/USART3_CK/LCD_S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), K2.6
PB13: IC1.G8 (PB13/SPI2_SCK/USART3_CTS/LCD_SEG13/TIM9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), K2.4
PB14: IC1.F8 (PB14/SPI2_MISO/USART3_RTS/LCD_SEG14/TIM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), K2.2
PB15: IC1.F7 (PB15/SPI2_MOSI/LCD_SEG15/TIM11_CH1/ADC_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), K2.3
PC0: IC1.E3 (PC0/LCD_SEG18/ADC_IN10/COMP1_INP), K3.6
PC1: IC1.E2 (PC1/LCD_SEG19/ADC_IN11/COMP1_INP), K3.1
PC2: IC1.F2 (PC2/LCD_SEG20/ADC_IN12/COMP1_INP), K3.3
PC4: IC1.H5 (PC4/LCD_SEG22/ADC_IN14/COMP1_INP), K2.12
PC5: IC1.H6 (PC5/LCD_SEG23/ADC_IN15/COMP1_INP), K2.10
PC6: IC1.F6 (PC6/TIM3_CH1/LCD_SEG24), K1.2
PC7: IC1.E7 (PC7/TIM3_CH2/LCD_SEG25), K1.4
PC8: IC1.E8 (PC8/TIM3_CH3/LCD_SEG26), K1.3
PC9: IC1.D8 (PC9/TIM3_CH4/LCD_SEG27), K1.5
PC10: IC1.B7 (PC10/USART3_TX/LCD_SEG28/LCD_SEG40/LCD_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), K1.11
PC11: IC1.B6 (PC11/USART3_RX/LCD_SEG29/LCD_SEG41/LCD_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), K1.12
PC12: IC1.C5 (PC12/USART3_CK/LCD_SEG30/LCD_SEG42/LCD_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), K1.16
PC13: IC1.A2 (PC13-WKUP2/PC13/RTC_TAMP1/RTC_TS/RTC_OU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), K4.4
PD2: IC1.B5 (PD2/TIM3_ETR/LCD_SEG31/LCD_SEG43/LCD_CO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), K1.14
SWCLK: IC1.A7 (PA14/JTCK-SWCLK), K5.4 (TCK/SWCLK), K7.1
SWDIO: IC1.A8 (PA13/JTMS-SWDIO), K5.2 (TMS/SWDIO), K6.2
VDD: C5.2, C6.2, IC1.D2 (VDD_4), IC1.E4 (VDD_3), IC1.E5 (VDD_2), IC1.E6 (VDD_1), J1.1, J2.1, K1.1, K5.1 (VTG), K7.2
VDDA: C7.2, IC1.H1 (VDDA), J2.2
VLCD: C8.2, IC1.B2 (VLCD), J1.2
VREF+: IC1.G1 (VREF+), K3.4
